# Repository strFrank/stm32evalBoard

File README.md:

# stm32evalBoard
Attempt to make a PCB for experiments using STM32F446RET

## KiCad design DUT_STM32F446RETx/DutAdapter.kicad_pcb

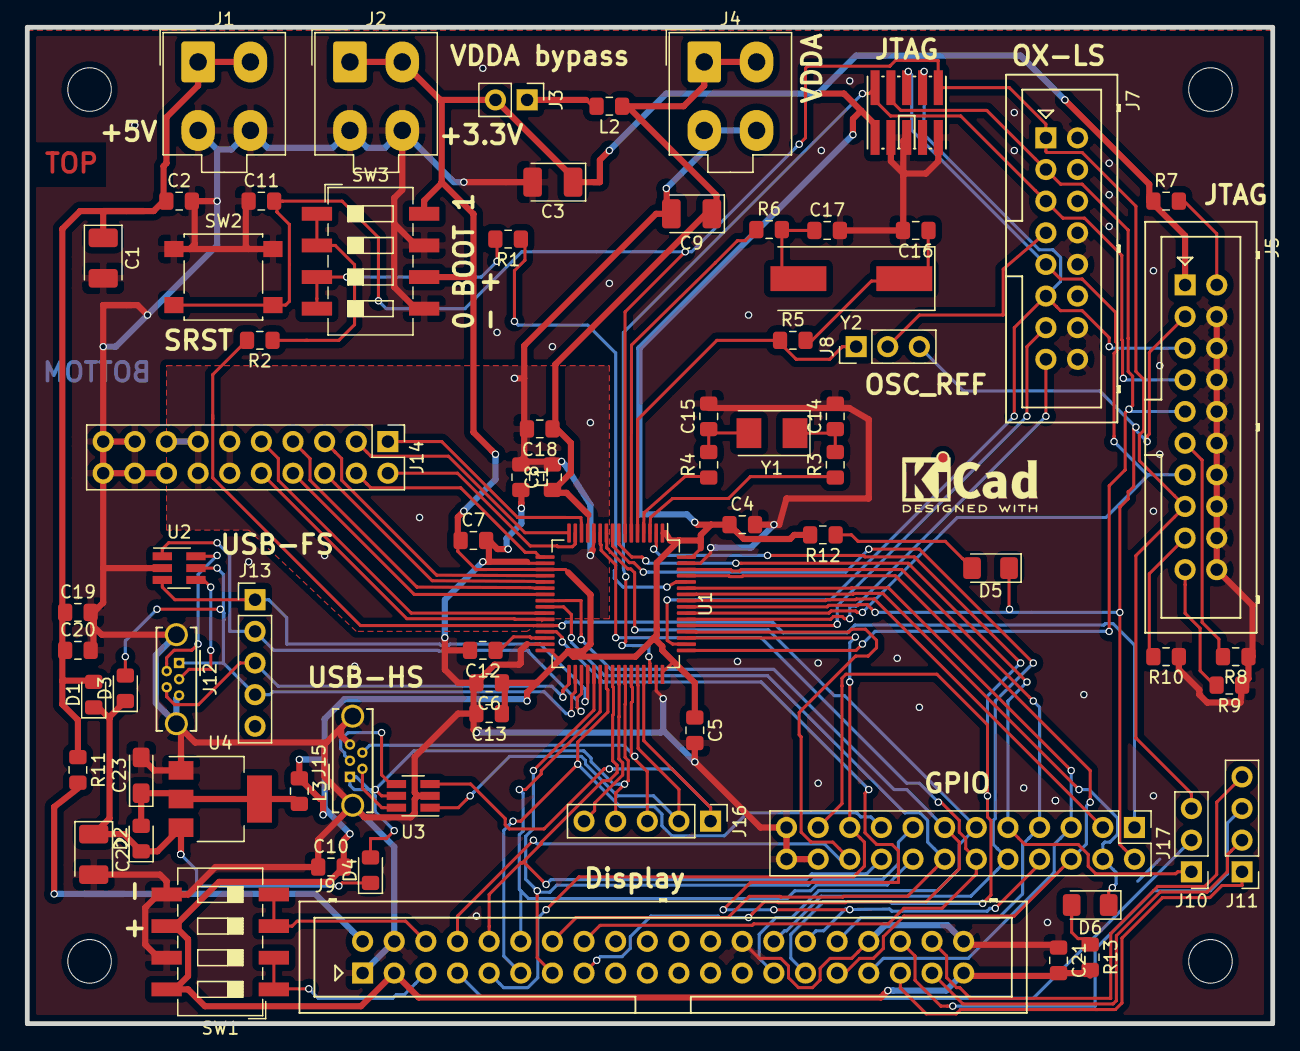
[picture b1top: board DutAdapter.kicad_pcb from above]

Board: 2 copper layers, 100.0 x 80.0 mm, 71 parts (0 on the bottom side), 86 nets.

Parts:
C1, C3, C9, C22: 10u; CP_EIA-3528-15_AVX-H_Pad1.50x2.35mm_HandSolder
C2, C4, C5, C6, C7, C8, C10, C11, C20, C21: 100n; C_0805_2012Metric_Pad1.15x1.40mm_HandSolder
C12, C13, C18, C19: 4u7 l-ESR; C_0805_2012Metric_Pad1.15x1.40mm_HandSolder
C14, C15: 1.5p; C_0805_2012Metric_Pad1.15x1.40mm_HandSolder
C16, C17: 27p; C_0805_2012Metric_Pad1.15x1.40mm_HandSolder
C23: 22u; CP_EIA-3216-18_Kemet-A_Pad1.58x1.35mm_HandSolder
D1, D2, D3, D4: D_Schottky; D_0805_2012Metric_Pad1.15x1.40mm_HandSolder
D5, D6: LED; LED_1206_3216Metric_Pad1.42x1.75mm_HandSolder
J1, J2, J4: Conn_01x04; Molex_Mini-Fit_Jr_5566-04A_2x02_P4.20mm_Vertical
J3: Conn_01x02_Male; PinHeader_1x02_P2.54mm_Vertical
J5: Conn_ARM_JTAG_SWD_20; Multicomp_MC9A12-2034_2x10_P2.54mm_Vertical
J6: JTAG_SWD_02x05_Samtec; FTSH-105-XX-X-DV
J7: OX_02x08_Odd_Even; Multicomp_MC9A12-1634_2x08_P2.54mm_Vertical
J8, J10: Conn_01x03_Male; PinHeader_1x03_P2.54mm_Vertical
J9: Conn_02x20_Odd_Even; Multicomp_MC9A12-4034_2x20_P2.54mm_Vertical
J11: Conn_01x04_Male; PinHeader_1x04_P2.54mm_Vertical
J12, J15: USB_B_Micro; USB_Micro-B_Wuerth_614105150721_Vertical_CircularHoles
J13, J16: Conn_01x05; PinHeader_1x05_P2.54mm_Vertical
J14: Conn_02x10_Top_Bottom; PinHeader_2x10_P2.54mm_Vertical
J17: Conn_02x12_Odd_Even; PinHeader_2x12_P2.54mm_Vertical
L1, L2, L3: Ferrite_Bead; L_0805_2012Metric_Pad1.15x1.40mm_HandSolder
R1, R2, R7, R8, R9, R10: 10k; R_0805_2012Metric_Pad1.15x1.40mm_HandSolder
R3, R4, R5, R6: 0R; R_0805_2012Metric_Pad1.15x1.40mm_HandSolder
R11, R12, R13: 100; R_0805_2012Metric_Pad1.15x1.40mm_HandSolder
SW1, SW3: SW_DIP_x04; SW_DIP_SPSTx04_Slide_6.7x11.72mm_W8.61mm_P2.54mm_LowProfile
SW2: SW_Push; SW_SPST_B3S-1000
U1: STM32F446RETx; LQFP-64_10x10mm_P0.5mm
U2, U3: USBLC6-2SC6; SOT-23-6_Handsoldering
U4: AZ1117-3.3; SOT-223-3_TabPin2
Y1: 32.768kHz; Crystal_SMD_5032-2Pin_5.0x3.2mm
Y2: 8MHz; Crystal_SMD_HC49-SD

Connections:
+3V3: C3.1, C4.1, C5.1, C6.1, C7.1, C10.2, C13.1, C21.2, J2.1, J2.2, J3.2, J5.1, J6.1, J9.3, J9.39, L3.1, R7.1, R12.2, R13.2, SW1.6, SW1.8, SW3.6, SW3.8, U1.1, U1.19, U1.32, U1.48, U1.64
+5V: C1.1, C2.1, C19.1, C20.1, D1.2, J1.1, J1.2, R11.1
/ADC1_IN0: J14.1, U1.14
/ADC1_IN1: J14.2, U1.15
/ADC1_IN2: J14.3, U1.16
/ADC1_IN3: J14.4, U1.17
/ADC2_IN6: J14.7, U1.22
/ADC2_IN7: J14.8, U1.23
/ADC2_IN8: J14.9, U1.26
/ADC2_IN9: J14.10, U1.27
/DAC_OUT0: J14.5, U1.20
/DAC_OUT1: J14.6, U1.21
/DB9: J9.16, J17.12, U1.11
/DB10: J9.15, J17.13, U1.24
/DB11: J9.14, J17.14, U1.25
/DB12: J9.13, J17.15, U1.37
/DB13: J9.12, J17.16, U1.38
/DB14: J9.11, J17.17, U1.39
/DB15: J9.10, J17.18, U1.40
/DB16: J9.9, J17.19, U1.51
/DB17: J9.8, J17.20, U1.52
/FMARK: J9.33, J17.5, U1.59
/LCD-CS: J9.32, J17.7, U1.62
/LCD-NRD: J9.29, J17.21, U1.2
/LCD-RS: J9.31, J17.6, U1.61
/LCD-nRST: J9.7, J10.2
/LCD_MISO: J9.27, J17.11, U1.10
/LCD_MOSI: J9.28, J17.10, U1.9
/LCD_RESET: J10.1, J17.9, U1.8
/LCD_SCL: J9.30, J17.8, U1.29
/NRST: C11.2, J5.15, J6.10, J7.1, J10.3, SW2.2, U1.7
/PB2: J17.1, R2.2, U1.28
/PB4: D5.1, J5.3, J8.3, J17.2, U1.56
/PB5: J17.3, U1.57
/PB6: D6.1, J17.4, U1.58
/RCC_OSC_REF: J8.1, R5.1, U1.5
/TCLK_SWCLK: J5.9, J6.4, J7.3, U1.49
/TDI: J5.5, J6.8, J7.11, U1.50
/TDO_SWO: J5.13, J6.6, J7.9, U1.55
/TMS_SWDIO: J5.7, J6.2, J7.5, U1.46
/UART_RX: J7.15, U1.54
/UART_TX: J7.13, U1.53
/USBOTG_FS_DM: J16.2, U1.44, U3.1
/USBOTG_FS_DP: J16.1, U1.45, U3.3
/USBOTG_FS_ID: J15.4, J16.3, U1.43
/USBOTG_FS_SOF: J16.5, U1.41
/USBOTG_FS_VBUS: D4.2, J15.1, J16.4, U1.42, U3.5
/USBOTG_HS_DM: J13.2, U1.35, U2.1
/USBOTG_HS_DP: J13.1, U1.36, U2.3
/USBOTG_HS_ID: J12.4, J13.3, U1.33
/USBOTG_HS_VBUS: D3.2, J12.1, J13.4, U1.34, U2.5
/VUSB5P: C22.1, D1.1, D2.1, D3.1, D4.1, U4.3
/X+: J9.35, J11.1
/X-: J9.37, J11.2
/Y+: J9.36, J11.3
/Y-: J9.38, J11.4
GND: C1.2, C2.2, C3.2, C4.2, C5.2, C6.2, C7.2, C10.1, C11.1, C12.2, C13.2, C14.2, C15.2, C16.2, C17.2, C19.2, C20.2, C21.1, C22.2, C23.2, J1.3, J1.4, J2.3, J2.4, J5.4, J5.6, J5.8, J5.10, J5.12, J5.14, J5.16, J5.18, J5.20, J6.3, J6.5, J6.9, J7.2, J7.4, J7.6, J7.8, J7.10, J7.12, J7.14, J7.16, J9.1, J9.4, J9.26, J9.34, J9.40, J12.5, J12.6, J14.16, J14.17, J14.18, J14.19, J14.20, J15.5, J15.6, J17.22, J17.23, J17.24, L1.2, R8.1, R9.1, R10.1, SW1.5, SW1.7, SW2.1, SW3.5, SW3.7, U1.18, U1.31, U1.47, U1.63, U2.2, U3.2, U4.1
GNDA: C8.2, C9.2, C18.2, J4.3, J4.4, J14.11, J14.12, J14.13, J14.14, J14.15, L1.1, U1.12
unnamed: C12.1, U1.30
unnamed: C14.1, R3.2, Y1.1
unnamed: C15.1, R4.2, Y1.2
unnamed: C16.1, R5.2, Y2.1
unnamed: C17.1, R6.2, Y2.2
unnamed: C23.1, D2.2, L3.2, U4.2
unnamed: D5.2, R12.1
unnamed: D6.2, R13.1
unnamed: J3.1, L2.2
unnamed: J5.2, R7.2
unnamed: J5.11, R8.2
unnamed: J5.17, R10.2
unnamed: J5.19, R9.2
unnamed: J7.7, J8.2
unnamed: J9.2, R11.2
unnamed: J9.5, SW1.1, SW1.2
unnamed: J9.6, SW1.3, SW1.4
unnamed: J12.2, U2.6
unnamed: J12.3, U2.4
unnamed: J15.2, U3.6
unnamed: J15.3, U3.4
unnamed: R1.1, U1.60
unnamed: R1.2, SW3.3, SW3.4
unnamed: R2.1, SW3.1, SW3.2
unnamed: R3.1, U1.3
unnamed: R4.1, U1.4
unnamed: R6.1, U1.6
VDDA: C8.1, C9.1, C18.1, J4.1, J4.2, L2.1, U1.13

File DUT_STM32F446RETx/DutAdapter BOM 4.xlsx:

Item | Qty | Reference(s) | Value | LibPart | Footprint | Datasheet | Digikey_PN | MPN | Manufacturer
1 | 4 | C1, C3, C9, C22 | 10u | Device:CP | Capacitor_Tantalum_SMD:CP_EIA-3528-15_AVX-H_Pad1.50x2.35mm_HandSolder | http://datasheets.avx.com/TPS.pdf | 478-2398-1-ND | TPSB106K016R0800 | AVX
2 | 10 | C2, C4, C5, C6, C7, C8, C10, C11, C20, C21 | 100n | Device:C | Capacitor_SMD:C_0805_2012Metric_Pad1.15x1.40mm_HandSolder | https://content.kemet.com/datasheets/KEM_C1002_X7R_SMD.pdf | 311-1140-1-ND | CC0805KRX7R9BB104
3 | 4 | C12, C13, C18, C19 | 4u7 l-ESR | Device:C | Capacitor_SMD:C_0805_2012Metric_Pad1.15x1.40mm_HandSolder | https://content.kemet.com/datasheets/KEM_C1006_X5R_SMD.pdf | 399-3133-1-ND | C0805C475K8PACTU
4 | 2 | C14, C15 | 1.5p | Device:C | Capacitor_SMD:C_0805_2012Metric_Pad1.15x1.40mm_HandSolder | http://www.yageo.com/documents/recent/UPY-GP_NP0_16V-to-50V_16.pdf | 311-4126-1-ND | CC0805BRNPO9BN1R5
5 | 2 | C16, C17 | 27p | Device:C | Capacitor_SMD:C_0805_2012Metric_Pad1.15x1.40mm_HandSolder | http://datasheets.avx.com/AutoU_Series.pdf | 478-3844-1-ND | 08052U270JAT2A
6 | 1 | C23 | 22u | Device:CP | Capacitor_Tantalum_SMD:CP_EIA-3216-18_Kemet-A_Pad1.58x1.35mm_HandSolder | http://datasheets.avx.com/TPS.pdf | 478-11579-1-ND | TPSA226K010R0900 | AVX
7 | 4 | D1, D2, D3, D4 | D_Schottky | Device:D_Schottky | Diode_SMD:D_0805_2012Metric_Pad1.15x1.40mm_HandSolder | http://datasheets.avx.com/schottky.pdf | 478-7800-1-ND | SD0805S020S1R0 | AVX
8 | 2 | D5, D6 | LED | Device:LED | LED_SMD:LED_1206_3216Metric_Pad1.42x1.75mm_HandSolder | ~ | 160-1168-1-ND | LTST-C150EKT
9 | 3 | J1, J2, J4 | Conn_01x04 | Connector_Generic:Conn_01x04 | Connector_Molex:Molex_Mini-Fit_Jr_5566-04A_2x02_P4.20mm_Vertical | https://www.molex.com/molex/products/datasheet.jsp?part=acti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 | WM3801-ND | 39-28-1043 | Molex
10 | 1 | J3 | Conn_01x02_Male | Connector:Conn_01x02_Male | Connector_PinHeader_2.54mm:PinHeader_1x02_P2.54mm_Vertical | https://www.molex.com/molex/products/datasheet.jsp?part=acti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 | WM50014-02-ND | 22-28-4020 | Molex
11 | 1 | J5 | Conn_ARM_JTAG_SWD_20 | Connector:Conn_ARM_JTAG_SWD_20 | Connector_Multicomp:Multicomp_MC9A12-2034_2x10_P2.54mm_Vertical | https://datasheet.octopart.com/TST-110-01-L-D-Samtec-datashe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 | SAM10837-ND | TST-110-01-L-D | Samtec
12 | 1 | J6 | JTAG_SWD_02x05_Samtec | Connector:Conn_ARM_JTAG_SWD_10 | modules:FTSH-105-XX-X-DV | http://suddendocs.samtec.com/catalog_english/ftsh_mt.pdf | SAM9438-ND | FTSH-105-01-L-DV-007-K | Samtec
13 | 1 | J7 | OCST_02x08_Odd_Even | Connector_Generic:Conn_02x08_Odd_Even | Connector_Multicomp:Multicomp_MC9A12-1634_2x08_P2.54mm_Vertical | http://datasheet.octopart.com/TSW-108-07-F-D-Samtec-datashee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 | SAM10854-ND | TSW-108-07-F-D | Samtec
14 | 2 | J8, J10 | Conn_01x03_Male | Connector:Conn_01x03_Male | Connector_PinHeader_2.54mm:PinHeader_1x03_P2.54mm_Vertical | https://www.molex.com/molex/products/datasheet.jsp?part=acti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 | WM4589-ND | 22-28-4035 | Molex
15 | 1 | J9 | Conn_02x20_Odd_Even | Connector_Generic:Conn_02x20_Odd_Even | Connector_Multicomp:Multicomp_MC9A12-4034_2x20_P2.54mm_Vertical | https://cdn.amphenol-icc.com/media/wysiwyg/files/drawing/67996.pdf | 609-4925-ND | 67996-140HLF | Amphenol ICC
16 | 1 | J11 | Conn_01x04_Male | Connector:Conn_01x04_Male | Connector_PinHeader_2.54mm:PinHeader_1x04_P2.54mm_Vertical | http://www.chipquik.com/datasheets/HDR100IMP40M-G-V-TH.pdf | HDR100IMP40M-G-V-TH-ND | HDR100IMP40M-G-V-TH | Chipquick
17 | 2 | J12, J15 | USB_B_Micro | Connector:USB_B_Micro | Connector_USB:USB_Micro-B_Wuerth_614105150721_Vertical_CircularHoles | https://katalog.we-online.de/em/datasheet/614105150721.pdf | 732-5958-1-ND | 614105150721
18 | 2 | J13, J16 | Conn_01x05 | Connector_Generic:Conn_01x05 | Connector_PinHeader_2.54mm:PinHeader_1x05_P2.54mm_Vertical | ~
19 | 1 | J14 | Conn_02x10_Top_Bottom | Connector_Generic:Conn_02x10_Top_Bottom | Connector_PinHeader_2.54mm:PinHeader_2x10_P2.54mm_Vertical | ~
20 | 1 | J17 | Conn_02x12_Odd_Even | Connector_Generic:Conn_02x12_Odd_Even | Connector_PinHeader_2.54mm:PinHeader_2x12_P2.54mm_Vertical | ~
21 | 3 | L1, L2, L3 | Ferrite_Bead | Device:Ferrite_Bead | Inductor_SMD:L_0805_2012Metric_Pad1.15x1.40mm_HandSolder | https://product.tdk.com/info/en/catalog/datasheets/beads_com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 | 445-1564-1-ND | MPZ1608S101ATAH0
22 | 6 | R1, R2, R7, R8, R9, R10 | 10k | Device:R | Resistor_SMD:R_0805_2012Metric_Pad1.15x1.40mm_HandSolder |  | 541-3015-1-ND | CRCW080510K0FKEA
23 | 4 | R3, R4, R5, R6 | 0R | Device:R | Resistor_SMD:R_0805_2012Metric_Pad1.15x1.40mm_HandSolder |  | 311-0.0CRCT-ND | RC0805FR-070RL
24 | 3 | R11, R12, R13 | 100 | Device:R | Resistor_SMD:R_1206_3216Metric_Pad1.42x1.75mm_HandSolder |  | RNCP1206FTD100RCT-ND | RNCP1206FTD100R
25 | 2 | SW1, SW3 | SW_DIP_x04 | Switch:SW_DIP_x04 | Button_Switch_SMD:SW_DIP_SPSTx04_Slide_6.7x11.72mm_W8.61mm_P2.54mm_LowProfile | https://www.ctscorp.com/wp-content/uploads/219.pdf | CT3116CT-ND | 219-4LPSTR | CTS Electrocomponents
26 | 1 | SW2 | SW_Push | Switch:SW_Push | Button_Switch_SMD:SW_SPST_B3S-1000 | http://www.te.com/commerce/DocumentDelivery/DDEController?Ac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 | 450-1804-ND | 1825910-7
27 | 1 | U1 | STM32F446RETx | MCU_ST_STM32F4:STM32F446RETx | Package_QFP:LQFP-64_10x10mm_P0.5mm |  | 497-15376-ND | STM32F446RET6
28 | 2 | U2, U3 | USBLC6-2SC6 | Power_Protection:USBLC6-2SC6 | Package_TO_SOT_SMD:SOT-23-6_Handsoldering | http://www2.st.com/resource/en/datasheet/CD00050750.pdf | 497-5235-1-ND | USBLC6-2SC6
29 | 1 | U4 | AZ1117-3.3 | Regulator_Linear:AZ1117-3.3 | Package_TO_SOT_SMD:SOT-223-3_TabPin2 | https://www.diodes.com/assets/Datasheets/AZ1117.pdf | AZ1117H-3.3TRE1DICT-ND | AZ1117H-3.3TRE1
30 | 1 | Y1 | 32.768kHz | Device:Crystal | Crystal:Crystal_SMD_5032-2Pin_5.0x3.2mm | https://support.epson.biz/td/api/doc_check.php?dl=brief_FC-1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 | 535-11937-1-ND | ABS07-120-32.768KHZ-T
31 | 1 | Y2 | 8MHz | Device:Crystal | Crystal:Crystal_SMD_HC49-SD | https://abracon.com/Resonators/abls.pdf | 535-10212-1-ND | ABLS-8.000MHZ-B4-T

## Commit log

2019-08-10 save my first STM32 project to github
2019-08-10 version change in layout file, too.
